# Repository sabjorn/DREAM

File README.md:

## D.R.E.A.M - *D*ata *R*ules *E*verything *A*round *M*e

## About
*dreamIO* is an ESP8266 based development board for designing interactive art applications. 

The board features MPU-6050 6-Axis IMU, TPS61200 Voltage Regulator, MCP73831 Lipo Charger, and 12x WS2812B RGB LEDs. 

The functionality of the board is made available through an OSC based API. Through this network interface, large, complex, and distributed interactive applications can be developed with little (to no) microcontroller programming. Instead, designers can use any language of their choice (any languague which supports UDP messaging) and any platform of their choice (Mac, Windows, Linux) to write the software which communicates with these devices. 

## Development Status
Early development stages, version 0.~

**Note**: The current PCB design in the git is broken from an attempt to fix 

### Arduino SDK info
Currently only version **2.0.0** of ESP8266 for Arduino is supported for this project. 

## External Libraries
* [ESP8266 Arduino](https://github.com/esp8266/Arduino) - 2.0.0
* [I2CDev](https://github.com/jrowberg/i2cdevlib) for the MPU-6050
* [OSC](https://github.com/CNMAT/OSC) 
* [Adafruit NeoPixels](https://github.com/adafruit/Adafruit_NeoPixel) - 1.0.6 **Use the Arduino Package Manager version**

## Future
The addition of a haptics motor is likely.

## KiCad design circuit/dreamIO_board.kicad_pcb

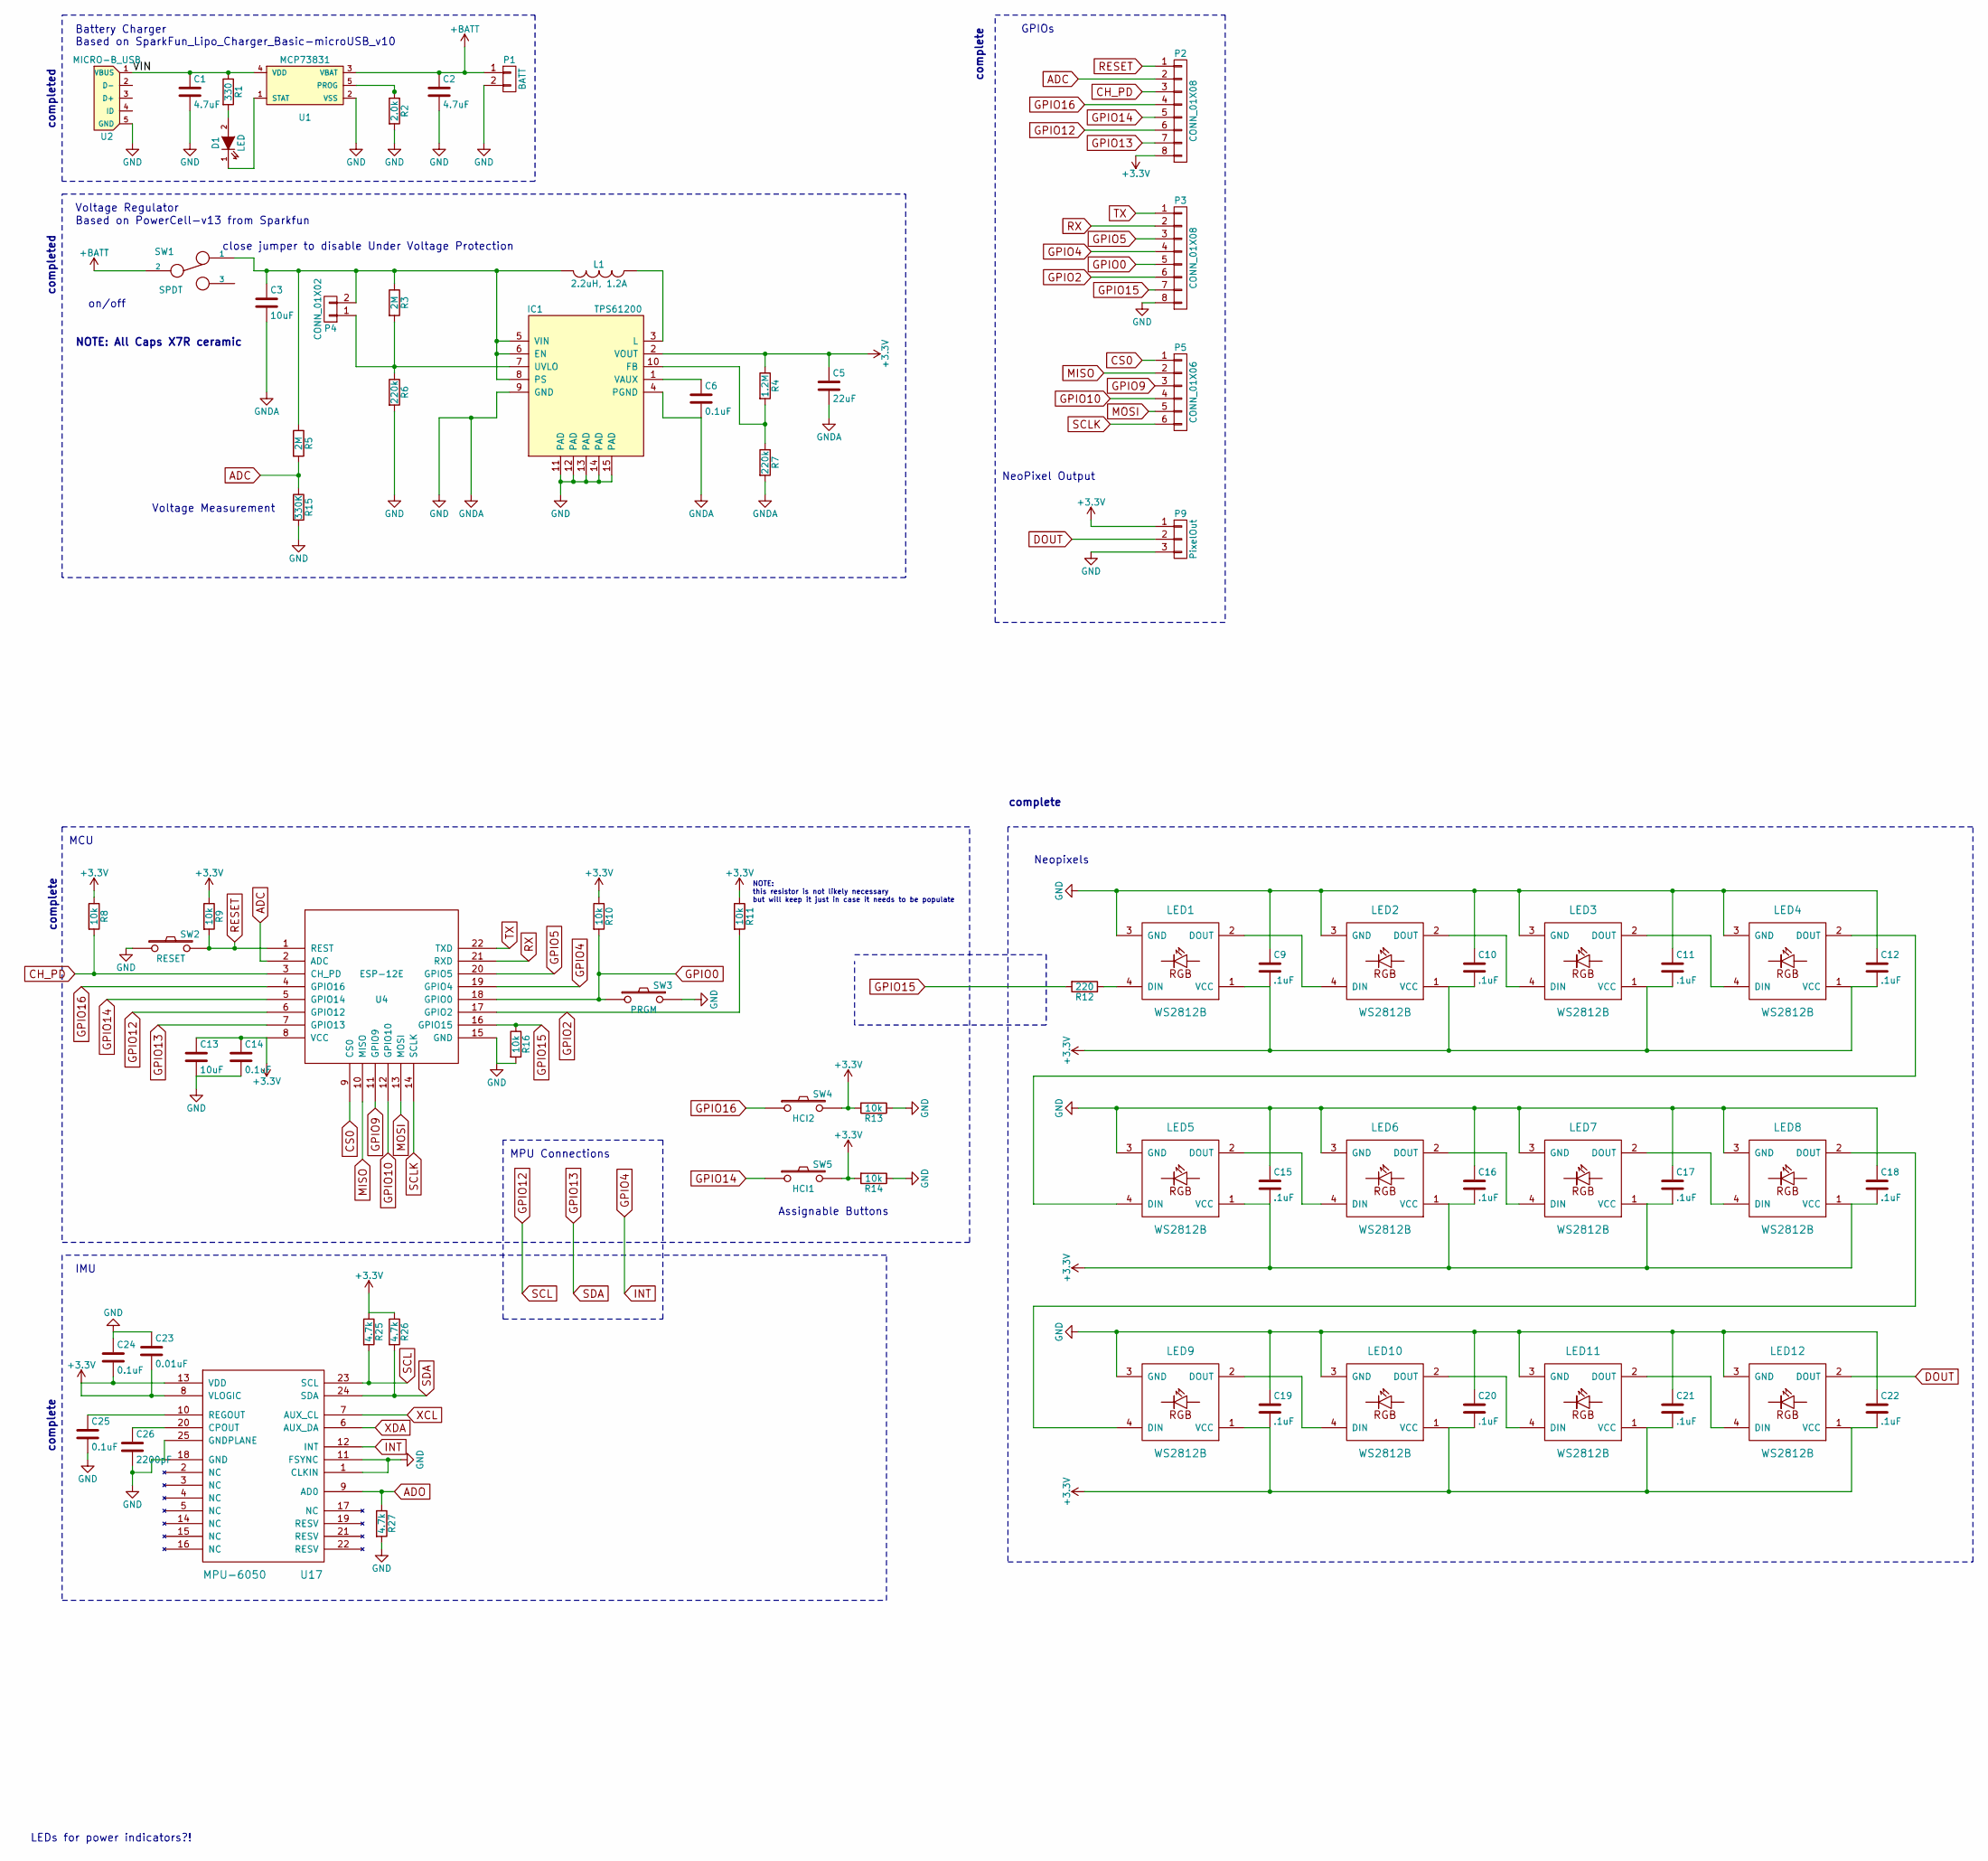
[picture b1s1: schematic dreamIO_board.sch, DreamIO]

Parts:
C1, C2: 4.7uF; 0603
C3, C13: 10uF; 0603
C5: 22uF; 0603
C6, C14, C24, C25: 0.1uF; 0603
C9, C10, C11, C12, C15, C16, C17, C18, C19, C20, C21, C22: .1uF; 0603
C23: 0.01uF; 0603
C26: 2200pF; 0603
D1: LED; 0603
IC1: TPS61200; tps61200_QFN-10_PAD
L1: 2.2uH, 1.2A; 1206E
LED1, LED2, LED3, LED4, LED5, LED6, LED7, LED8, LED9, LED10, LED11, LED12: WS2812B; WS2812B_LED
P1: BATT; Pin_Header_Straight_1x02
P2, P3: CONN_01X08; _Pin2mm_8
P4: CONN_01X02; _Solder_Pad2.54_2
P5: CONN_01X06; _Pin2mm_6
P9: PixelOut; PIN_ARRAY_3X1
R1: 330; 0603
R2: 2.0k; 0603
R3, R5: 2M; 0603
R4: 1.2M; 0603
R6, R7: 220k; 0603
R8, R9, R10, R11, R13, R14, R16: 10k; 0603
R12: 220; 0603
R15: 330K; 0603
R25, R26, R27: 4.7k; 0603
SW1: SPDT; DPST_TE_SSJ12R04
SW2: RESET; SW_06_SMD
SW3: PRGM; SW_06_SMD
SW4: HCI2; SW_06_SMD
SW5: HCI1; SW_06_SMD
U1: MCP73831; SOT23-5
U2: MICRO-B_USB
U4: ESP-12E
U17: MPU-6050; QFN-24-4x4-EP_steevedit

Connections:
+3V3: C5.1, C9.2, C10.2, C11.2, C12.2, C13.1, C14.1, C15.2, C16.2, C17.2, C18.2, C19.2, C20.2, C21.2, C22.2, C23.2, C24.2, IC1.2 (VOUT), LED1.1 (VCC), LED2.1 (VCC), LED3.1 (VCC), LED4.1 (VCC), LED5.1 (VCC), LED6.1 (VCC), LED7.1 (VCC), LED8.1 (VCC), LED9.1 (VCC), LED10.1 (VCC), LED11.1 (VCC), LED12.1 (VCC), P2.8, P9.1, R4.1, R8.1, R9.1, R10.1, R11.1, R13.2, R14.2, R25.1, R26.1, SW4.2, SW5.2, U4.8 (VCC), U17.8 (VLOGIC), U17.13 (VDD)
+BATT: C2.1, P1.1, SW1.2, U1.3 (VBAT)
/VIN: C1.1, R1.1, U1.4 (VDD), U2.1 (VBUS)
ADC: P2.2, R5.2, R15.1, U4.2 (ADC)
ADO: R27.1, U17.9 (AD0)
CH_PD: P2.3, R8.2, U4.3 (CH_PD)
CS0: P5.1, U4.9 (CS0)
DOUT: LED12.2 (DOUT), P9.2
GND: C1.2, C2.2, C3.2, C5.2, C6.2, C9.1, C10.1, C11.1, C12.1, C13.2, C14.2, C15.1, C16.1, C17.1, C18.1, C19.1, C20.1, C21.1, C22.1, C23.1, C24.1, C25.2, C26.2, IC1.4 (PGND), IC1.9 (GND), IC1.11 (PAD), IC1.12 (PAD), IC1.13 (PAD), IC1.14 (PAD), IC1.15 (PAD), LED1.3 (GND), LED2.3 (GND), LED3.3 (GND), LED4.3 (GND), LED5.3 (GND), LED6.3 (GND), LED7.3 (GND), LED8.3 (GND), LED9.3 (GND), LED10.3 (GND), LED11.3 (GND), LED12.3 (GND), P1.2, P3.8, P9.3, R2.2, R6.2, R7.2, R13.1, R14.1, R15.2, R16.2, R27.2, SW2.1, SW3.2, U1.2 (VSS), U2.5 (GND), U4.15 (GND), U17.1 (CLKIN), U17.11 (FSYNC), U17.18 (GND), U17.25 (GNDPLANE)
GPIO0: P3.5, R10.2, SW3.1, U4.18 (GPIO0)
GPIO2: P3.6, R11.2, U4.17 (GPIO2)
GPIO4: P3.4, U4.19 (GPIO4), U17.12 (INT)
GPIO5: P3.3, U4.20 (GPIO5)
GPIO9: P5.3, U4.11 (GPIO9)
GPIO10: P5.4, U4.12 (GPIO10)
GPIO12: P2.6, R25.2, U4.6 (GPIO12), U17.23 (SCL)
GPIO13: P2.7, R26.2, U4.7 (GPIO13), U17.24 (SDA)
GPIO14: P2.5, SW5.1, U4.5 (GPIO14)
GPIO15: P3.7, R12.2, R16.1, U4.16 (GPIO15)
GPIO16: P2.4, SW4.1, U4.4 (GPIO16)
MISO: P5.2, U4.10 (MISO)
MOSI: P5.5, U4.13 (MOSI)
unnamed: C3.1, IC1.5 (VIN), IC1.6 (EN), IC1.8 (PS), L1.2, P4.2, R3.1, R5.1, SW1.1
unnamed: C6.1, IC1.1 (VAUX)
unnamed: C25.1, U17.10 (REGOUT)
unnamed: C26.1, U17.20 (CPOUT)
unnamed: D1.1 (K), U1.1 (STAT)
unnamed: D1.2 (A), R1.2
unnamed: IC1.3 (L), L1.1
unnamed: IC1.7 (UVLO), P4.1, R3.2, R6.1
unnamed: IC1.10 (FB), R4.2, R7.1
unnamed: LED1.2 (DOUT), LED2.4 (DIN)
unnamed: LED1.4 (DIN), R12.1
unnamed: LED2.2 (DOUT), LED3.4 (DIN)
unnamed: LED3.2 (DOUT), LED4.4 (DIN)
unnamed: LED4.2 (DOUT), LED5.4 (DIN)
unnamed: LED5.2 (DOUT), LED6.4 (DIN)
unnamed: LED6.2 (DOUT), LED7.4 (DIN)
unnamed: LED7.2 (DOUT), LED8.4 (DIN)
unnamed: LED8.2 (DOUT), LED9.4 (DIN)
unnamed: LED10.2 (DOUT), LED11.4 (DIN)
unnamed: LED9.2 (DOUT), LED10.4 (DIN)
unnamed: LED11.2 (DOUT), LED12.4 (DIN)
unnamed: R2.1, U1.5 (PROG)
RESET: P2.1, R9.2, SW2.2, U4.1 (REST)
RX: P3.2, U4.21 (RXD)
SCLK: P5.6, U4.14 (SCLK)
TX: P3.1, U4.22 (TXD)

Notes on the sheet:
Battery Charger Based on SparkFun_Lipo_Charger_Basic-microUSB_v10
close jumper to disable Under Voltage Protection
Based on PowerCell-v13 from Sparkfun
Voltage Regulator
on/off
completed
NOTE: All Caps X7R ceramic
Neopixels
IMU
complete
NOTE: this resistor is not likely necessary but will keep it just in case it needs to be populate
MCU
GPIOs
LEDs for power indicators?!
MPU Connections
NeoPixel Output
Assignable Buttons
Voltage Measurement

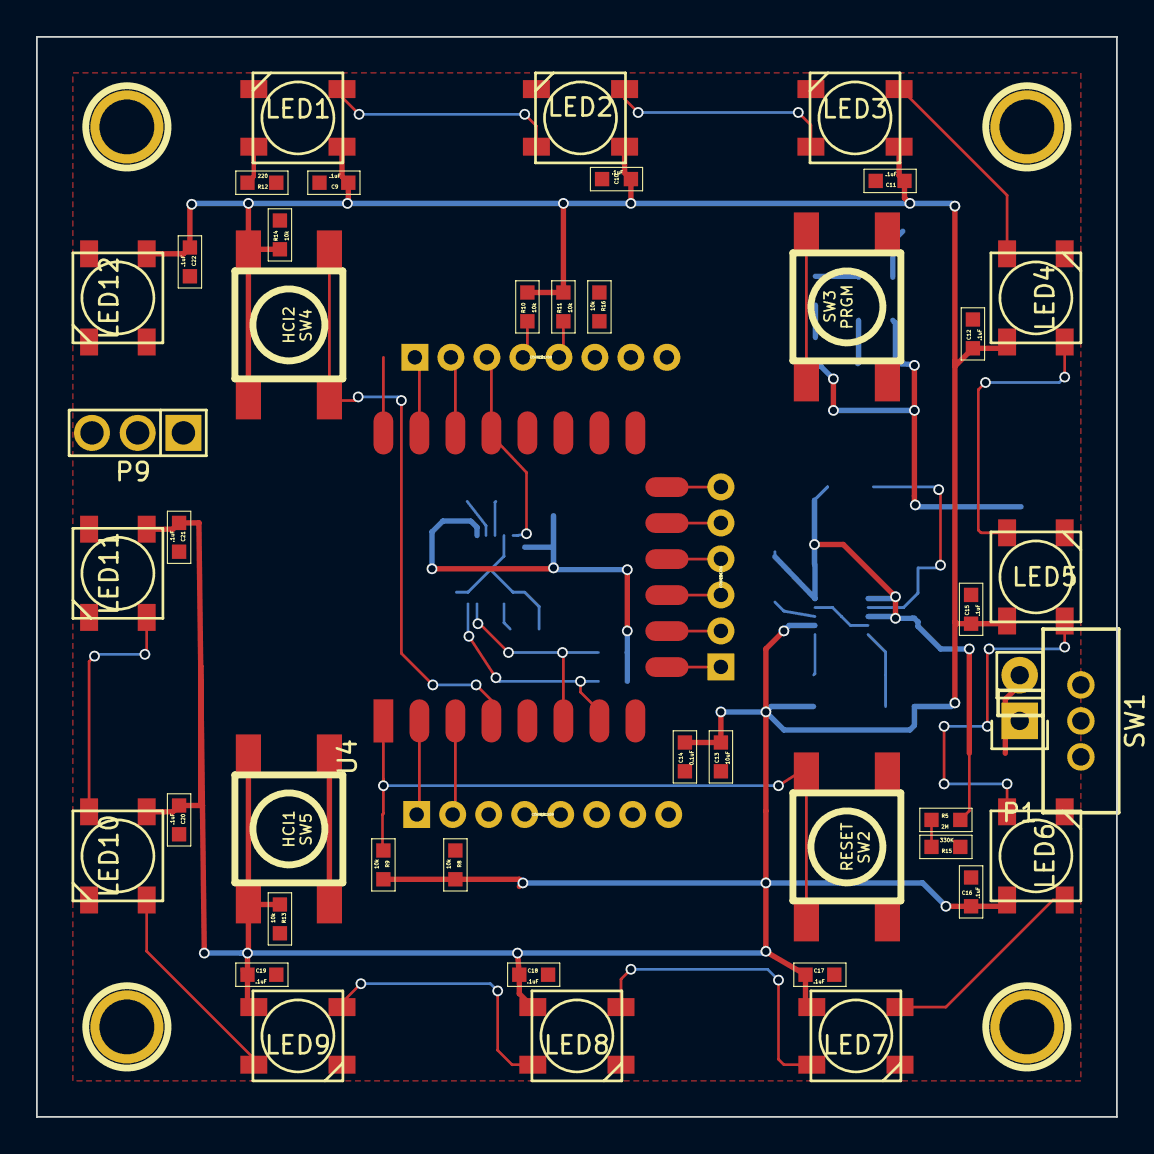
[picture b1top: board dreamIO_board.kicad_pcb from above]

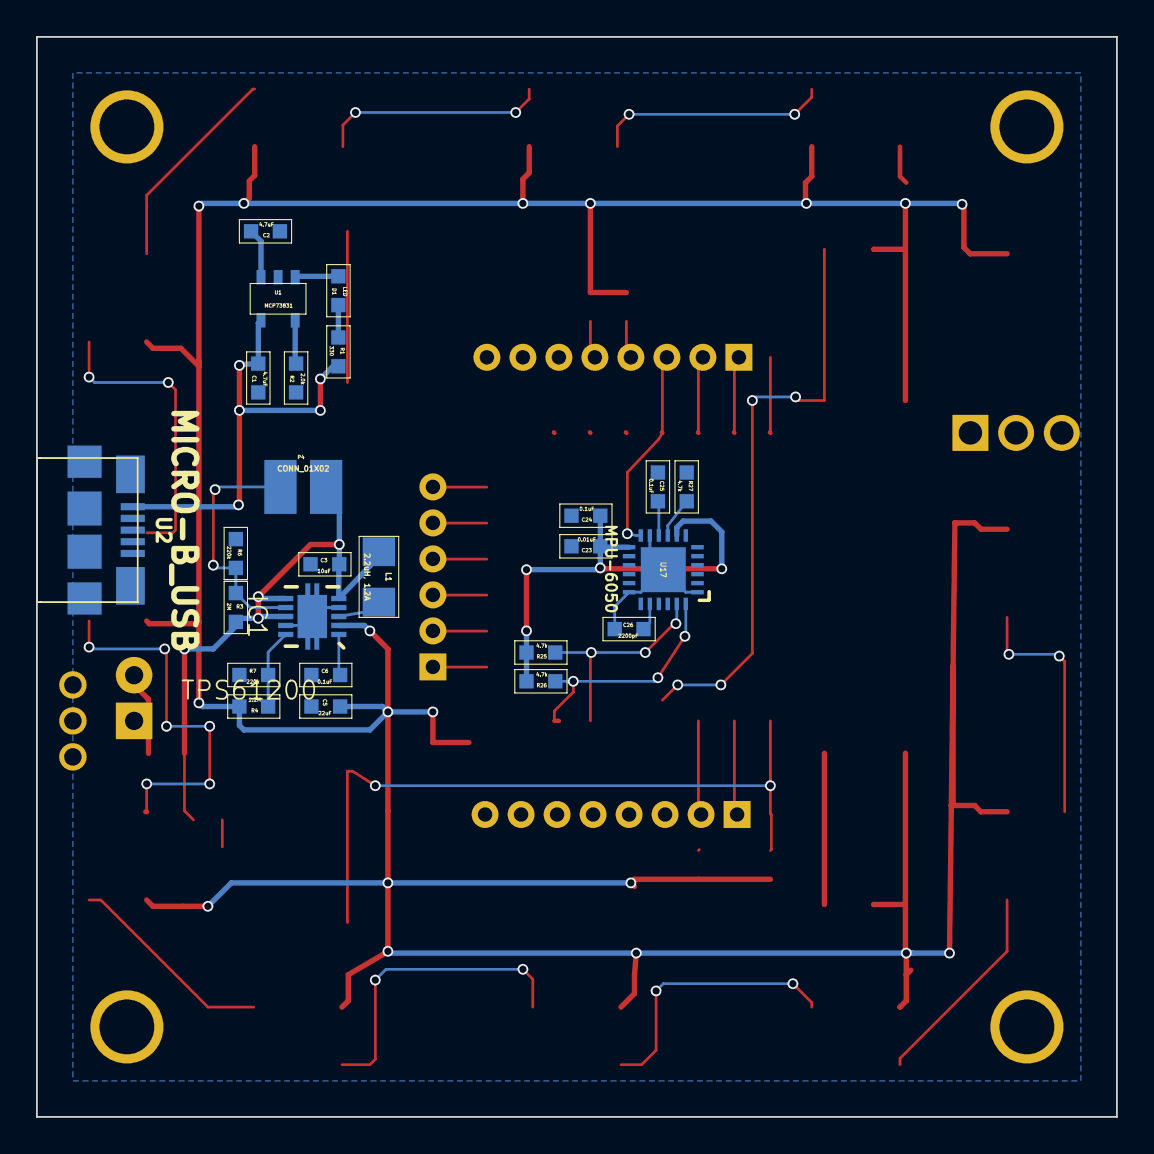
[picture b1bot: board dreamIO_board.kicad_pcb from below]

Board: 2 copper layers, 60.0 x 60.0 mm, 76 parts (25 on the bottom side), 48 nets.

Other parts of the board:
H4, H4#2, H4#3, H4#4: SCREWHOLE; 1pin

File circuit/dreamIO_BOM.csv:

"Id","Designator","Package","Quantity","Designation","Supplier and ref",
1,"C1,C2","0603",2,"4.7uF",
2,"C3,C13","0603",2,"10uF",
3,"C5","0603",1,"22uF",
4,"C6,C9,C10,C11,C12,C14,C15,C16,C17,C18,C19,C20,C21,C22,C24,C25","0603",16,"0.1uF",
5,"C23","0603",1,"0.01uF",
6,"C26","0603",1,"2200pF",
7,"IC1","tps61200_QFN-10_PAD",1,"TPS61200",
8,"L1","1206E",1,"2.2uH, 1.2A",
9,"LED1,LED2,LED3,LED4,LED5,LED6,LED7,LED8,LED9,LED10,LED11,LED12","WS2812B_LED",12,"WS2812B",
10,"P1","Pin_Header_Straight_1x02",1,"BATT",
11,"P9","Pin_Header_Straight_1x03",1,"PixelOut",
12,"R1","0603",1,"330",
13,"R2","0603",1,"2.0k",
14,"R3,R5","0603",2,"2M",
15,"R4","0603",1,"1.2M",
16,"R6,R7","0603",2,"220k",
17,"R8,R9,R10,R11,R16,R13,R14","0603",7,"10k",
18,"R12","0603",1,"220",
19,"R25,R26,R27","0603",3,"4.7k",
20,"U1","SOT23-5",1,"MCP73831",
21,"U2","MICRO-B_USB",1,"MICRO-B_USB",
22,"U4","ESP-12E",1,"ESP-12E",
23,"D1","0603",1,"LED",
24,"P2,P3","_Pin2mm_8",2,"CONN_01X08",
25,"P5","_Pin2mm_6",1,"CONN_01X06",
26,"P4","_Solder_Pad2.54_2",1,"CONN_01X02",
27,"SW2","SW_06_SMD",1,"RESET",
28,"SW3","SW_06_SMD",1,"PRGM",
29,"H4,H4,H4,H4","1pin",4,"SCREWHOLE",
30,"SW1","DPST_TE_SSJ12R04",1,"SPDT",
31,"SW4","SW_06_SMD",1,"HCI2",
32,"SW5","SW_06_SMD",1,"HCI1",
33,"U17","QFN-24-4x4-EP_steevedit",1,"MPU-6050",
34,"R15","0603",1,"330K",

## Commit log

2015-12-19 added OSC control examples
2015-12-19 added readme for OSC example
2015-12-20 added MPU6050 example
2015-12-22 stream/recieve works
2015-12-28 added control of individual neopixels
2015-12-29 fixed missing ;
2015-12-29 added Max/MSP example for communciating with ESP8266 using OSC Bundles
2015-12-29 changed OSCexample code to better reflect the current development board
2015-12-30 added image for GPIO requirements of ESP8266
2015-12-31 edited a variable to make more clear
2016-01-04 added example code of OSCMessages on ESP8266
2016-01-06 added a throttle to maxpatch to prevent excessive message speed. Also added example patch for controlling a 3D object with jit.gl
2016-01-06 edited readme for style
2016-01-07 added an example for a device without an MPU. This device has controllable NeoPixels
2016-01-28 added dreamIO max sub-patch and help file for easy instantiation of dreamIO system
2016-01-31 added unique OSC ID for each object as #define
2016-02-22 changed OSC out to Bundle from Message. This should be more consistant.
2016-02-22 changed OSC API slighty and added an OSC endpoint to change the update rate. Also, changed the dreamIO.maxpat to better reflect the design style of most max objects (single input)
2016-04-03 got most of circuit schematic finished
2016-04-03 forgot to add the circuit design to git.
2016-04-04 finished circuit schematic. Needs review
2016-04-10 added notes and updated circuit design
2016-04-10 accidently added a file I didn't want and now it's gone
2016-04-10 removed some references (not owned by me) accidently added during a commit
2016-04-17 added custom footprint for tsp61200 regulator
2016-04-17 changed name of footprint file
2016-04-17 fixed IC1 footprint
2016-04-18 grouped PCB components together for board:
2016-05-09 finished layout
2016-05-16 added human input buttons
2016-05-16 moved the on off switch
2016-05-16 tried to get leds to work on one of the demo units. for some reason they just are nott working
2016-05-16 fixed the problem with the LEDs on the other board. Turns out the OSCNeoPixelExample had not been updated to the new API (which is present in the max/patch)
2016-05-16 realized the cascaded regulators might not be necessary since the output of the Neopixels at 3.3v is quite bright. While 5V would be brighter, it may not always be necessary to buy the extra parts
2016-05-25 changed pinout for MPU6050 to include groundplane under area. started on routing
2016-05-25 routed some traces. May need to go back in and clean some up.
2016-05-26 removed the 3.3V regulator. The TPS61200 is now the main regulator and will be 5V.
2016-05-26 added ADC voltage measurement. A voltage resistor of R1 2M and R2 330K keeps the maximum voltage of the battery (4.2V) below the 1V maximum for the analog pin. If the resistor network is not populate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
2016-05-26 changed position of on-off switch, batt connection, and USB input. Realized the USB plug didn`t have to be right in the center of one side
2016-05-26 laid a few more traces. roughly 78 to go;
2016-05-26 laid a few more traces. 50~ to go
2016-05-26 had to add the bak and sch files for the circuit. not sure why they were not added before
2016-05-26 removed a (seemingly) extra capacitor from TPS section. Emulated the layout for TPS from datasheet. roughly 40 connections to go. wooooo!
2016-05-27 finished board layout
2016-05-27 added gerber exports and moved all exports intended to be printed to a new directory
2016-05-27 added more print info
2016-05-30 added BOM
2016-05-30 changed formatting of BOM csv. replacing the ; with ,
2016-05-30 fixed svg outputs of PCB for printing
2016-06-04 added laser cutting case file and a large set of different symbols to try
2016-06-07 created a solder_stencil set for making mylar solder-paste stencils. Also, switched all 2mm headers on PCB to 2.54mm headers. Have not yet finished rerouting from this change
2016-06-15 fixed error on board: neopixel out did not have 3.3v output
2016-06-21 not sure what I did. have really messed up on keeping track of changes. I will do better by making branches! I think mostly what happened is there were some edits to the PCB which still needs to be r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
2016-06-30 edited the main code a little and got a final version of the installation box ready
2016-07-14 got OTA updates working
2016-07-14 removed extra IP address stuff (decided to only have boxes broadcast. May add a way to configure the output IP for UDP/OSC as part of the API later)
2016-07-14 got rid of all the GPIO stuff, may be added back in later. Also changed starting scheduler time to 30ms
2016-07-14 caught one more reference to GPIOs
2016-07-14 removed ID base endpoint since mDNS now works and each board has a hostname through which to send OSC messages. Edited the Maxpatch example to reflect the change in API
2016-07-14 forgot to save the maxpatch with last merge
2016-07-16 added animation effects for OTA updates and wifi connection. it would be a good idea in the future to add an animation wrapper for the neopixels. these animations are likely to get recycled and havin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
2016-07-16 changed the default scheduler time to 25ms. seems to be a happy balance of performance just at the edge of perceptual chunkyness of data stream
2016-07-16 changed the README to better reflect the project
2016-07-16 fixed some minor edits
2016-07-16 fixed more formatting
2016-07-16 added measurement of voltage divider, scaled to the minimum and maximum values of the battery, 2.6 and 4.2 respectively.
2016-07-16 moved the preprocessor defines for batt measurement higher up in file
2016-07-16 changed the /time endpoint to send millis because micros was overflowing
2016-07-16 added the gerber and drill files for the working PCB. The current ki-cad files are mangled from some fixes that never happened.
2016-07-16 moved case files over to Transcode git
2016-07-16 added MIT license to project
2016-07-17 removed what appears to have been a hostname setup. The mDNS seems to work fine through OTA library.
2016-07-17 added reset as OSC endpoint and updated example maxpatch to allow for this change. Also, changed the point in the code which has an ifdef statement to choose between OSCMessage and OSCBundle in such 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
2016-07-17 added /debug endpoint in firmware and max object
2016-07-17 yaw/pitch/roll all now are [0,1] output
2016-07-17 added an OSC out that tells what side teh cube is currently on, /side
2016-07-17 added color select via Side api endpoint
2016-07-17 got the addressing for OSC worked out
2016-07-19 added python file for viewing, recording, and debugging OSC data from DreamIO. This will be the basis of the DreamIO python object
2016-07-19 removed a symlink
2016-07-19 cleaned up python OSC slightly
2016-07-19 commented out the default handlers in python osc
2016-07-20 got python record of OSC data working fairly well. should be turned into a utility
2016-07-21 adjusted dreamIO.maxpat to have an OSC-route object with the deviceID before routing the regular endpints
2016-07-21 got this utility to work
2016-07-21 got record script to send update time to dreamIO through OSC via command line. This will be useful for setting dreamIO recording at different rates (and with the LEDs)
2016-07-21 added color control to python. starting to look like the beginnings of the library
2016-07-21 added computers time to CSV output to track the beginning and end of time running. Can help find if internal clock of board is drifting.
2016-07-21 changed comment in ESP8266_OSCExample.ino while trying to understand why the voltage reading is going above 1 for /batt
2016-07-26 changed osc recorder to save files with better filename
2016-07-27 got rid of linux_time recording in OSC message record, ideally leads to better times
2016-07-28 began transition to possibly faster way of handling OSC recording
2016-07-28 got alternate recorder matched up with the pyOSC based one
2016-07-28 fixed bug in raw_osc.py that caused recorded outputs to be overwritten resulting in duplicate values being placed in csv file
2016-07-30 forgot that OSC uses uint64_t not uint32_t
2016-07-30 apparently the OSC library wants int not uint64_t. maybe not
2016-07-30 Changed API to count packets sent out via UDP.
2016-07-31 added a bunch of files that should have been there all along
2016-07-31 added more metrics for analysis of data record tests
2016-07-31 fixed some issues with files in the git
2016-07-31 got rid of another unnecessary file in the git
2016-07-31 fixed more file issues
2016-07-31 moved the location of an example file
2016-08-01 git ignore isnt supposed to be included in the repo?
2016-08-01 removed some more DS_Store
2016-08-07 tried a bunch of stuff to get getIntMotionStatus() but apparently it doesnt work. just write a software version for now
2016-08-09 added calculations to get gyroscope and accel values (including without gravity), OSC output for these values, and a function to convert these values (int16_t) to [-1,1]
2016-08-09 for some reason 0e2c16 is no longer working with this commit. likely the battery has gone low (although that is suspicious)
2016-08-09 found that gyroscope was set to sensativity of +- 2000. therefore, divided gyro value by 2000. now is [-1, 1]
2016-08-09 switched the x and z axis output for the OSC gyro message to match the ordering of YPR
2016-08-09 adjusted max object to better match the ordering of YPR, Gyro, Accel
2016-08-12 got brightness implemented. doesnt work very well because of the way the Neopixel library was written. Basically the pixel values in ram are scaled and then pushed out so they cant come back if set t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
2016-08-12 added HSL control via OSC endpoint
2016-08-12 basic motion sensing works. needs hysterisis
2016-08-12 started on class for checking for motion
2016-08-12 edited the maxpatch;
2016-08-14 got going on MotionState
2016-08-14 added data container for IMU
2016-08-14 began transition in framework to IMU data container instead of the variables.
2016-08-14 class completed ish. now integrating into main
2016-08-14 fixed fmod issue with shitty static function
2016-08-14 adjusted all the osc outputs to get values from new motionstate object
2016-08-14 commented out YPR stability. will fix another time
2016-08-14 updated maxpatch with API endpoints
2016-08-14 made some max examples for multiple cubes
2016-08-14 edited readme
2016-09-14 fixed master so the data stream can be recorded. This master is now stable
2018-01-29 feat(major_overhaul): tonnes up updates to improve firmware including:
    * added calculations to get gyroscope and accel values (including without gravity), OSC output for these values, and a function to convert these values (int16_t) to [-1,1]
    * found that gyroscope was set to sensativity of +- 2000. therefore, divided gyro value by 2000. now is [-1, 1]
    * switched the x and z axis output for the OSC gyro message to match the ordering of YPR
    * adjusted max object to better match the ordering of YPR, Gyro, Accel
    * got brightness implemented. doesnt work very well because of the way the Neopixel library was written. Basically the pixel values in ram are scaled and then pushed out so they can
